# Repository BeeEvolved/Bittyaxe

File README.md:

<h1 align="center">itty-bitty open-source Bitcoin miner</h1>

The **BittyAxe** is a compact ASIC miner inspired by the [BitAxe Gamma](https://github.com/bitaxeorg/bitaxeGamma) design. It harnesses the power of the **BM1370** ASIC chip to achieve hash rates of approximately **1.2 TH/s** with an energy efficiency of **15 J/TH**.

---

## Features
- Custom, open-source compact thermal solution specifically designed for the BittyAxe
- Compact, space-saving form factor
- High-performance BM1370 ASIC chip
- ~1.2 TH/s hash rate
- 15 J/TH energy efficiency

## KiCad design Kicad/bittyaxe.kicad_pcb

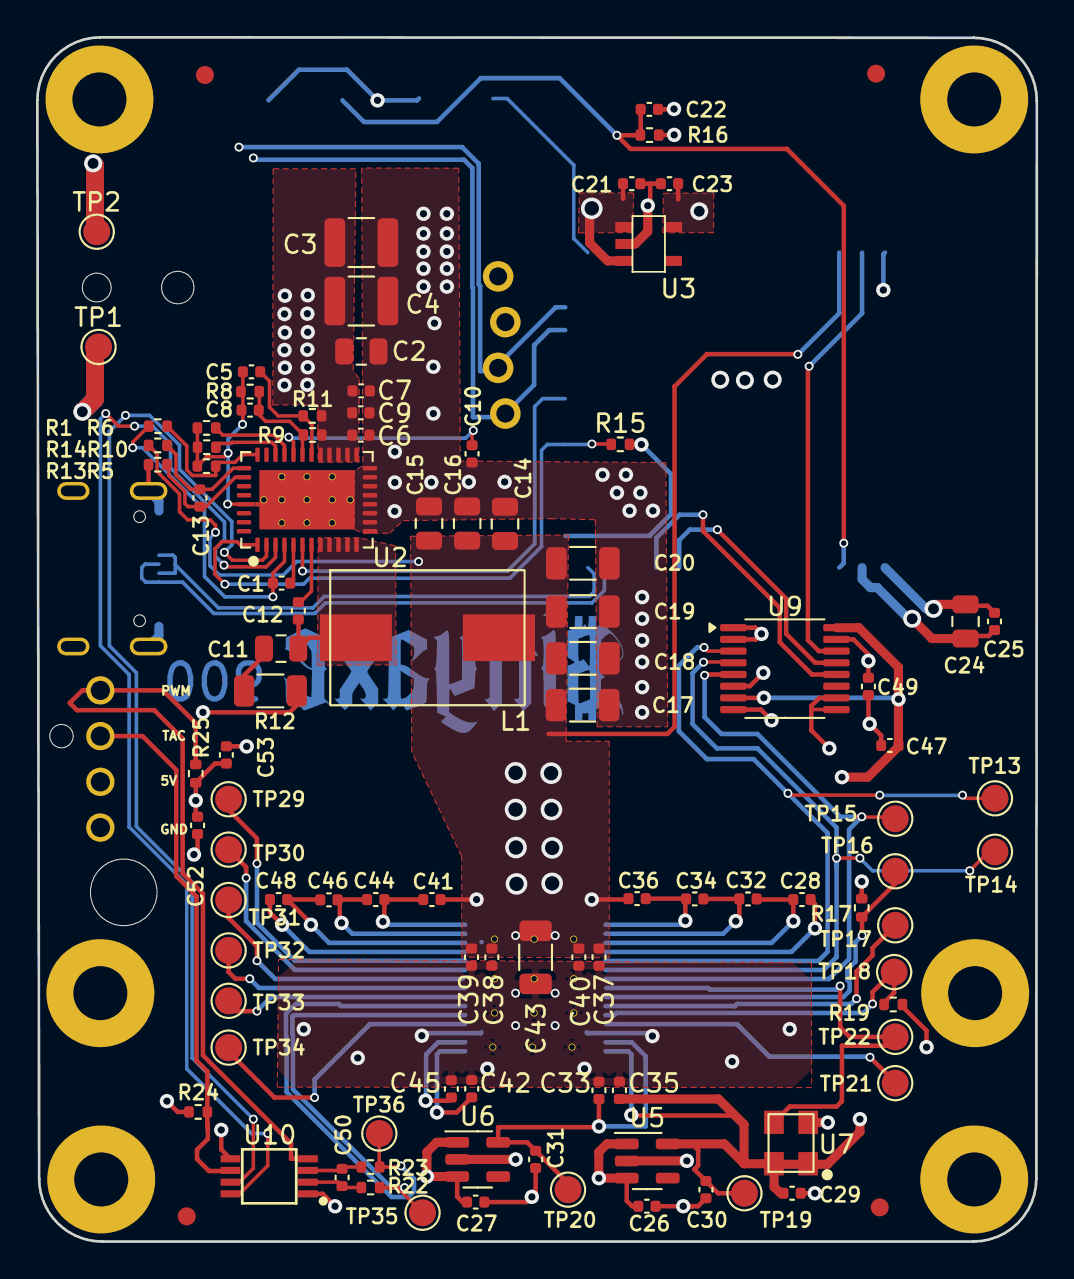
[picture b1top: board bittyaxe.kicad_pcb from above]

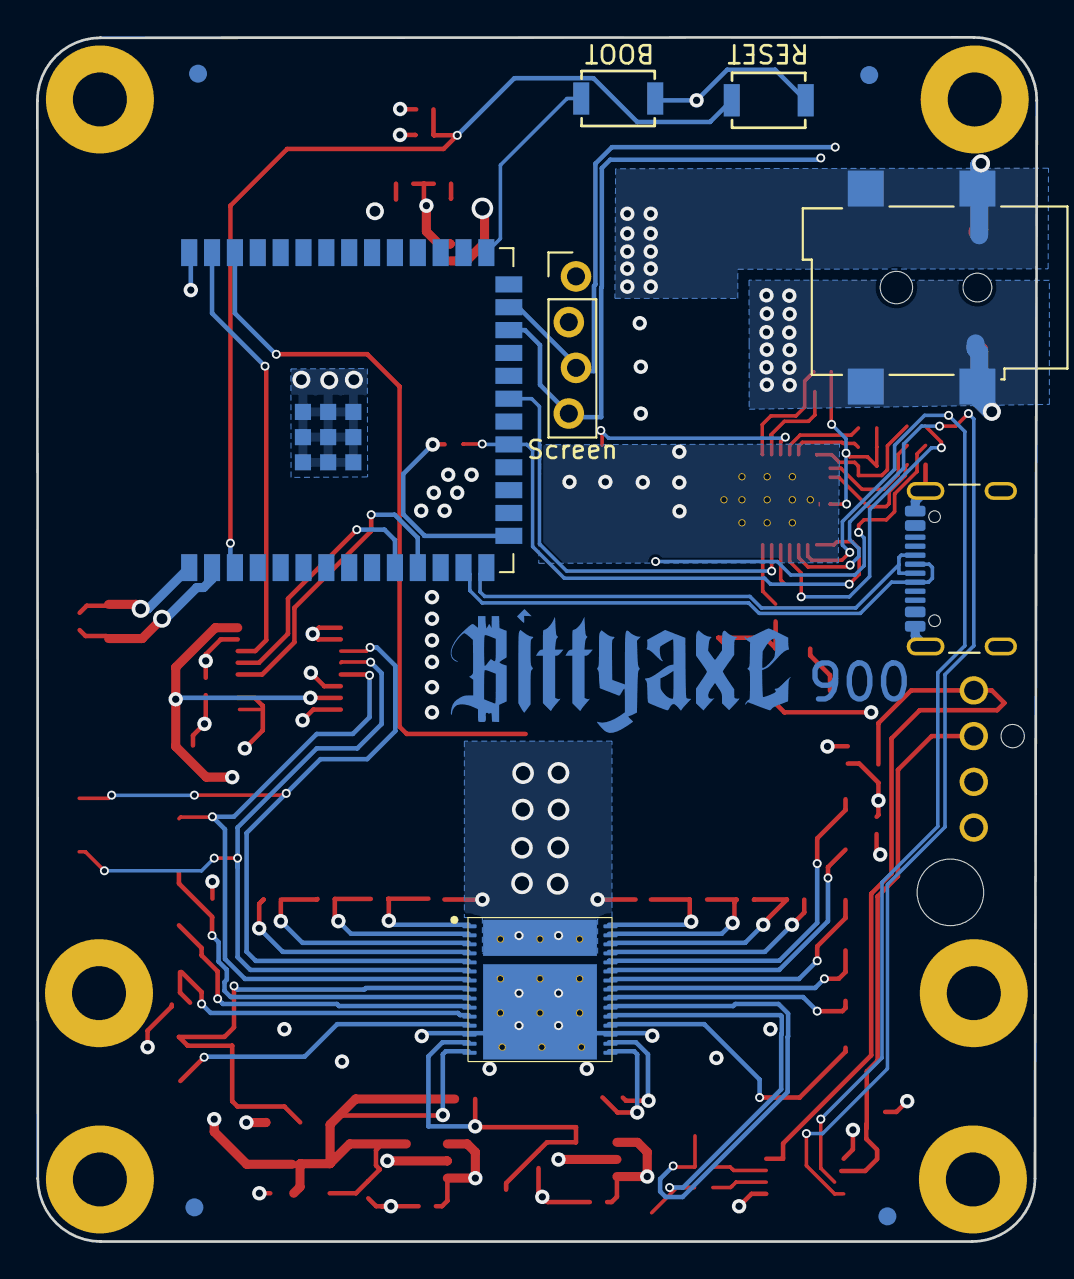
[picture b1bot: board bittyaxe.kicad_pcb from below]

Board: 4 copper layers, 55.5 x 66.9 mm, 122 parts (11 on the bottom side), 59 nets.

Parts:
C1, C5, C7, C21, C22, C23, C26, C27, C28, C30, C31, C32, C33, C34, C35, C36, C39, C40, C41, C42, C44, C45, C46, C48: 1uF; C_0402_1005Metric
C2, C24: 10uF; C_0805_2012Metric
C3, C4: 47uF; C_1210_3225Metric
C6: 4700pF; C_0402_1005Metric
C8, C12, C25, C29, C37, C38, C47, C49, C52, C53: 0.1uF; C_0402_1005Metric
C9: 2200pF; C_0402_1005Metric
C10: 4.7uF; C_0402_1005Metric
C11: 1000pF; C_0805_2012Metric
C13: 100pF; C_0402_1005Metric
C14, C15, C16: 22uF; C_0805_2012Metric
C17, C18, C19, C20, C43: 100uF; C_1206_3216Metric
C50: 470pF; C_0402_1005Metric
FID1, FID2, FID3, FID4, FID5, FID6, FID7, FID8: Fiducial; Fiducial_1mm_Mask2mm
Fan Cable Passthrough: MountingHole_3.7mm
H9, H9#2, H9#3, H9#4, H9#5, H9#6: MountingHole_Pad; MountingHole_3mm_Pad_Via
J1: 54-00164; TENSILITY_54-00164
J5: USB_C_Receptacle_USB2.0; USB_C_Receptacle_GCT_USB4105-xx-A
J6: Conn_01x04; 470531000
L1: 300nH; SLC1175-271MEC_COC
R1: 8.25k; R_0402_1005Metric
R5: 14.7k; R_0402_1005Metric
R6: RES 0 OHM JUMPER 1/16W; R_0402_1005Metric
R8: 3.74k; R_0402_1005Metric
R9: 11.8k; R_0402_1005Metric
R10: 68.1k; R_0402_1005Metric
R11: 10; R_0402_1005Metric
R12: 1; R_1206_3216Metric
R13, R14: 49.9; R_0402_1005Metric
R15, R16, R17, R25: 10k; R_0402_1005Metric
R19: 1k; R_0402_1005Metric
R22, R23: 100; R_0402_1005Metric
R24: 5.6k; R_0402_1005Metric
SW1, SW2: GT-TC029B-H025-L1N; SW_CS1213AGF260_CRS
Screen: Conn_01x04; PinHeader_1x04_P2.54mm_Vertical_shifted
T1: net-tie; NetTie-0.25mm
TP1, TP2, TP13, TP14, TP15, TP16, TP17, TP18, TP19, TP20, TP21, TP22, TP29, TP30, TP31, TP32, TP33, TP34, TP35, TP36: TestPoint; TestPoint_Pad_D1.5mm
U2: TPS546D24ARVFR; LQFN40-CLIP
U3: RT9080-33GJ5
U4: ESP32-S3-WROOM-1
U5: MCP1824T-1202E/OT; SOT-23-5
U6: MCP1824T-0802E; SOT-23-5
U7: 25MHz; SMD3225-4P
U8: BM1370_mode1; BM1370
U9: SN74AVC4T774; TSSOP-16_4.4x5mm_P0.65mm
U10: EMC2101; TSSOP-8_3x3mm_P0.65mm

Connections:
/3V3: C23.1, C24.1, C25.1, C49.1, R15.2, R16.1, R24.2, Screen.2, U3.5 (VOUT), U4.2 (3V3), U4.15 (GPIO3/TOUCH3/ADC1_CH2*), U9.15 (VCCB), U10.1 (VDD)
/5V: C2.1, C3.1, C4.1, C6.1, C7.1, C9.1, C21.1, C26.1, C27.1, C52.1, C53.1, J1.1, J6.2, R9.1, R11.1, R25.2, TP1.1, U2.21 (PVIN), U2.22 (PVIN), U2.23 (PVIN), U2.24 (PVIN), U2.25 (PVIN), U3.1 (VIN), U3.3 (EN), U5.1 (VIN), U5.3 (EN), U6.1 (VIN), U6.3 (EN)
/BM1370/0V8: C31.1, C33.1, TP20.1, U6.5 (VOUT), U8.14 (VDDIO_08_0)
/BM1370/1V2: C29.2, C30.1, C35.1, C47.1, TP19.1, U5.5 (VOUT), U7.1 (EN), U7.4 (VIN), U8.15 (VDDIO_12_0), U9.7 (DIR3), U9.16 (VCCA)
/BM1370/BI: R17.2, TP16.1, U8.9 (BI)
/BM1370/BO: TP33.1, U8.22 (BO)
/BM1370/CI: TP14.1, U8.6 (CI), U9.4 (A2)
/BM1370/CLKI: TP22.1, U7.3 (OUT), U8.8 (CLKI)
/BM1370/CLKO: TP32.1, U8.23 (CLKO)
/BM1370/CO: TP30.1, U8.25 (CO)
/BM1370/NRSTO: TP29.1, U8.26 (NRSTO)
/BM1370/PIN_MODE: TP34.1, U8.19 (PIN_MODE)
/BM1370/RI: TP31.1, U8.24 (RI)
/BM1370/RO: TP15.1, U8.7 (RO), U9.5 (A3)
/BM1370/RST_N: TP13.1, U8.5 (NRSTI), U9.3 (A1)
/BM1370/VDD1_0: C34.2, C36.1, U8.1 (VDD3_0)
/BM1370/VDD1_1: C41.2, C44.1, U8.30 (VDD3_1)
/BM1370/VDD2_0: C32.2, C34.1, U8.2 (VDD2_0)
/BM1370/VDD2_1: C44.2, C46.1, U8.29 (VDD2_1)
/BM1370/VDD3_0: C28.2, C32.1, U8.3 (VDD1_0)
/BM1370/VDD3_1: C46.2, C48.1, U8.28 (VDD1_1)
/ESP32/EN: C22.1, R16.2, SW1.2, U4.3 (EN)
/ESP32/IO0: SW2.2, U4.27 (GPIO0/BOOT*)
/ESP32/USB_D+: J5.A6 (D+), J5.B6 (D+), U4.14 (GPIO20/U1CTS/ADC2_CH9/CLK_OUT1/USB_D+)
/ESP32/USB_D-: J5.A7 (D-), J5.B7 (D-), U4.13 (GPIO19/U1RTS/ADC2_CH8/CLK_OUT2/USB_D-)
/Fan/FAN_PWM: J6.4, R25.1, U10.4 (FAN)
/Fan/FAN_TACH: J6.3, R24.1, U10.6 (ALERT/TACH)
/Fan/TEMP_DN: C50.2, R22.1, U10.3 (DN)
/Fan/TEMP_DP: C50.1, R23.2, U10.2 (DP)
/Fan/TEMP_N: R22.2, TP36.1, U8.21 (TEMP_N)
/Fan/TEMP_P: R23.1, TP35.1, U8.20 (TEMP_P)
/Power/AGND: C5.1, C8.2, R5.1, R6.2, R8.2, R10.2, T1.1, U2.37 (AGND)
/Power/PGOOD: R15.1, U2.1 (PGD), U4.19 (GPIO11/TOUCH11/ADC2_CH0/FSPID/FSPIIO5/S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)
/Power/PMB_ALRT: U2.6 (SMB_ALRT), U4.21 (GPIO13/TOUCH13/ADC2_CH2/FSPIQ/FSPIIO7/S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)
/Power/SW: C11.2, C12.2, L1.1, U2.8 (SW), U2.9 (SW), U2.10 (SW), U2.11 (SW), U2.12 (SW)
/RST: U4.39 (GPIO1/TOUCH1/ADC1_CH0), U9.14 (B1)
/RX: U4.11 (GPIO18/U1RXD/ADC2_CH7/CLK_OUT3), U9.12 (B3)
/SCL: Screen.3, U2.3 (PMB_CLK), U4.25 (GPIO48/SPICLK_N/SUBSPICLK_N_DIFF), U10.8 (SMCLK)
/SDA: Screen.4, U2.2 (PMB_DATA), U4.24 (GPIO47/SPICLK_P/SUBSPICLK_P_DIFF), U10.7 (SMDATA)
/TX: U4.10 (GPIO17/U1TXD/ADC2_CH6), U9.13 (B2)
/VDD: C14.1, C15.1, C16.1, C17.1, C18.1, C19.1, C20.1, C36.2, C37.1, C38.1, C39.1, C40.1, C41.1, C43.1, L1.2, R14.1, U4.38 (GPIO2/TOUCH2/ADC1_CH1), U8.31 (VDD), U8.33
GND: C2.2, C3.2, C4.2, C6.2, C7.2, C9.2, C10.2, C14.2, C15.2, C16.2, C17.2, C18.2, C19.2, C20.2, C21.2, C22.2, C23.2, C24.2, C25.2, C26.2, C27.2, C28.1, C29.1, C30.2, C31.2, C33.2, C35.2, C37.2, C38.2, C39.2, C40.2, C42.2, C43.2, C45.2, C47.2, C48.2, C49.2, C52.2, C53.2, H9.1, H9#2.1, H9#3.1, H9#4.1, H9#5.1, H9#6.1, J1.2, J1.3, J5.A1 (GND), J5.B1 (GND), J5.S1 (SHIELD), J6.1, R12.1, R13.2, R17.1, R19.1, SW1.1, SW2.1, Screen.1, T1.2, TP2.1, U2.13 (PGND), U2.14 (PGND), U2.15 (PGND), U2.16 (PGND), U2.17 (PGND), U2.18 (PGND), U2.19 (PGND), U2.20 (PGND), U2.41 (PAD), U3.2 (GND), U4.1 (GND), U4.40 (GND), U4.41 (GND), U5.2 (GND), U6.2 (GND), U7.2 (GND), U8.4 (VSS), U8.13 (PLL_VSS), U8.18 (VSS), U8.27 (VSS), U8.32 (VSS), U8.33, U9.1 (DIR1), U9.2 (DIR2), U9.6 (A4), U9.8 (DIR4), U9.9 (OE), U9.10 (GND), U10.5 (GND)
unnamed: C11.1, R12.2
unnamed: C5.2, R11.2, U2.26 (AVIN)
unnamed: C12.1, U2.7 (BOOT)
unnamed: C1.2, R1.1, U2.4 (BP1V5)
unnamed: C1.1, U2.5 (DRTN)
unnamed: C8.1, R8.1, R9.2, U2.27 (EN/UVLO)
unnamed: C13.2, R13.1, U2.34 (GOSNS)
unnamed: R1.2, R5.2, U2.32 (MSEL1)
unnamed: R6.1, U2.29 (MSEL2)
unnamed: C10.1, U2.28 (VDD5)
unnamed: C13.1, R14.2, U2.33 (VOSNS)
unnamed: R10.1, U2.30 (VSEL)
unnamed: TP21.1, U8.12 (INV_CLKO)
unnamed: R19.2, TP18.1, U8.11 (LITE_PAD)
unnamed: TP17.1, U8.10 (ROSC_SEL)
unnamed: C45.1, U8.17 (VDDIO_08_1)
unnamed: C42.1, U8.16 (VDDIO_12_1)

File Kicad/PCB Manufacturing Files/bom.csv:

Designator,Footprint,Quantity,Value,LCSC Part #
"C1, C21, C22, C23, C26, C27, C28, C30, C31, C32, C33, C34, C35, C36, C39, C40, C41, C42, C44, C45, C46, C48, C5, C7",0402,24,1uF,
C10,0402,1,4.7uF,
C11,0805,1,1000pF,
"C12, C25, C29, C37, C38, C47, C49, C52, C53, C8",0402,10,0.1uF,
C13,0402,1,100pF,
"C14, C15, C16",0805,3,22uF,
"C17, C18, C19, C20, C43",1206,5,100uF,
"C2, C24",0805,2,10uF,
"C3, C4",1210,2,47uF,
C50,0402,1,470pF,
C6,0402,1,4700pF,
C9,0402,1,2200pF,
J1,TENSILITY_54-00164,1,54-00164,C431534
J5,USB_C_Receptacle_GCT_USB4105-xx-A,1,USB_C_Receptacle_USB2.0,
J6,470531000,1,Conn_01x04,
L1,SLC1175-271MEC_COC,1,300nH,
R1,0402,1,8.25k,
R10,0402,1,68.1k,
R11,0402,1,10,
R12,1206,1,1,
"R13, R14",0402,2,49.9,
"R15, R16, R17, R25",0402,4,10k,
R19,0402,1,1k,
"R22, R23",0402,2,100,
R24,0402,1,5.6k,
R5,0402,1,14.7k,
R6,0402,1, RES 0 OHM JUMPER 1/16W,
R8,0402,1,3.74k,
R9,0402,1,11.8k,
SCREEN,PinHeader_1x04_P2.54mm_Vertical_shifted,1,Conn_01x04,
"SW1, SW2",SW_CS1213AGF260_CRS,2,GT-TC029B-H025-L1N,
U10,TSSOP-8_3x3mm_P0.65mm,1,EMC2101,
U2,LQFN40-CLIP,1,TPS546D24ARVFR,
U3,RT9080-33GJ5,1,RT9080-33GJ5,
U4,ESP32-S3-WROOM-1,1,ESP32-S3-WROOM-1,
U5,SOT-23-5,1,MCP1824T-1202E/OT,
U6,SOT-23-5,1,MCP1824T-0802E,
U7,SMD3225-4P,1,25MHz,C5137262
U8,BM1370,1,BM1370_mode1,
U9,TSSOP-16_4.4x5mm_P0.65mm,1,SN74AVC4T774,

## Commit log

2025-06-06 Create LICENSE
    CERN-OHL-S-2.0 license
2025-06-06 bittyaxe 900
2025-06-06 update main readme image
